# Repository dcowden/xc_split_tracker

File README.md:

# XC Tracker files

**xc_direct_esp32_receiver** uses an esp for compute, and an nrf52840 that reads the radio packets and sends them via uart
**xc_direct_radio_test_rx**  is the receiver 
**xc_direct_radio_test_tx** is  the transmitter
**xc_patriot_logger_nrf52840** is a try using ONLY the nrf52840, but i realized you cant use the radio and BLE, and since it also has no wifi its not a way forward
**xc_wifi_tracker_board_tests** Tests usingthe wifi tracker board-- really just getting the gps module working and printong on the screen

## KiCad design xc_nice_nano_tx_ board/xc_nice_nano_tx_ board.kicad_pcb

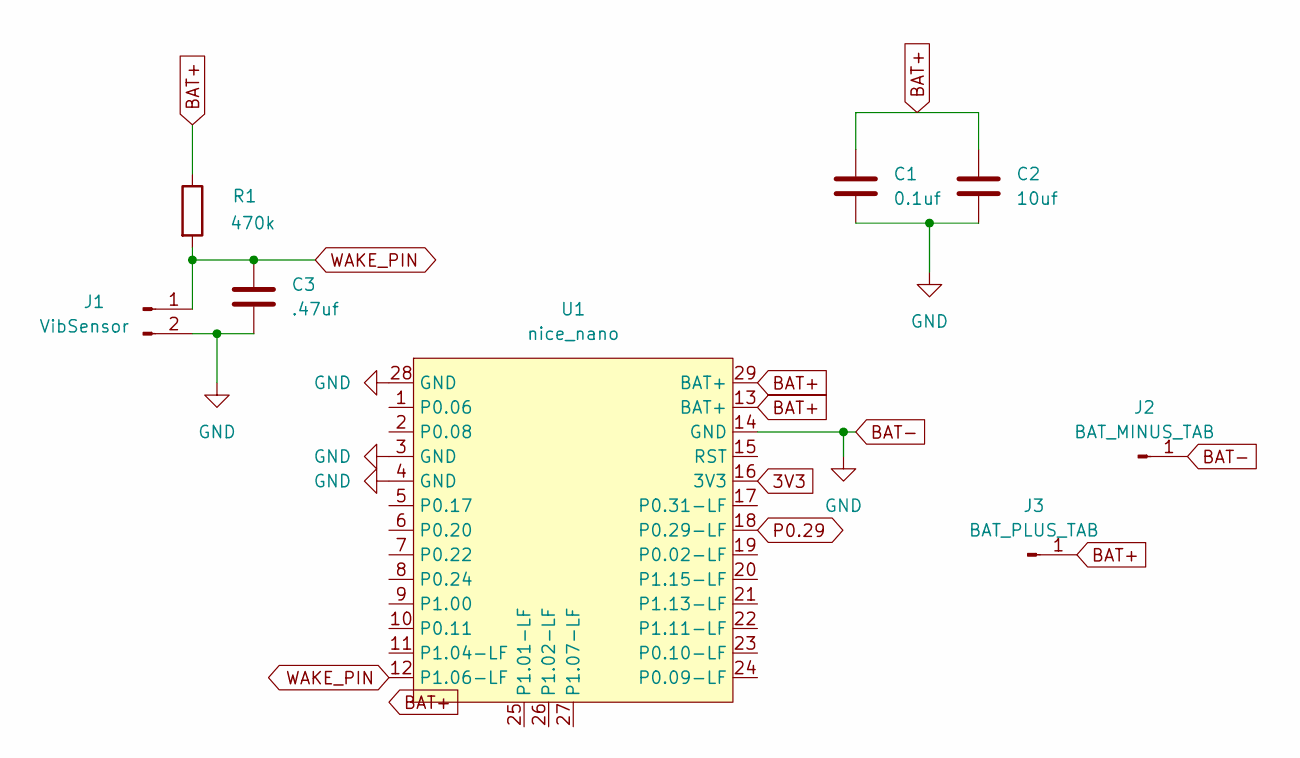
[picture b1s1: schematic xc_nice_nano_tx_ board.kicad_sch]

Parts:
C1: 0.1uf; C_0603_1608Metric
C2: 10uf; C_0603_1608Metric
C3: .47uf; C_0603_1608Metric
J1: VibSensor; CP_Radial_D5.0mm_P2.50mm
J2: BAT_MINUS_TAB; PinSocket_1x01_P2.54mm_Vertical
J3: BAT_PLUS_TAB; PinSocket_1x01_P2.54mm_Vertical
R1: 470k; R_0603_1608Metric
U1: nice_nano; nice_nano_AH_USBup

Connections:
3V3: U1.16 (3V3)
BAT+: C1.1, C2.1, J3.1, R1.1, U1.13 (BAT+), U1.29 (BAT+)
BAT-: C1.2, C2.2, C3.2, J1.2, J2.1, U1.3 (GND), U1.4 (GND), U1.14 (GND), U1.28 (GND)
P0.29: U1.18 (P0.29-LF)
WAKE_PIN: C3.1, J1.1, R1.2, U1.12 (P1.06-LF)

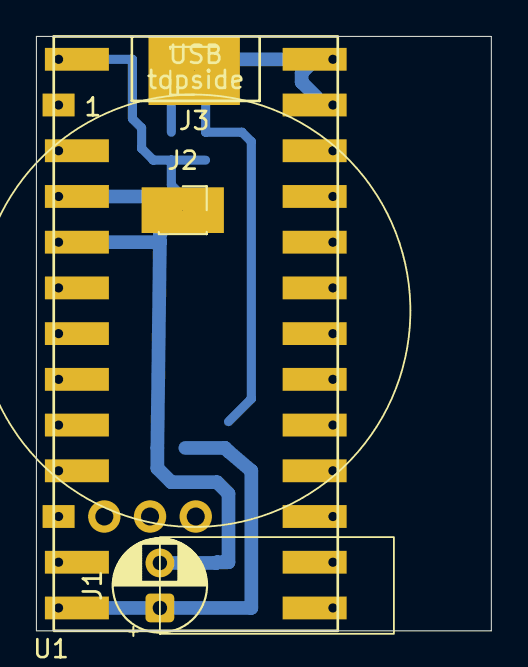
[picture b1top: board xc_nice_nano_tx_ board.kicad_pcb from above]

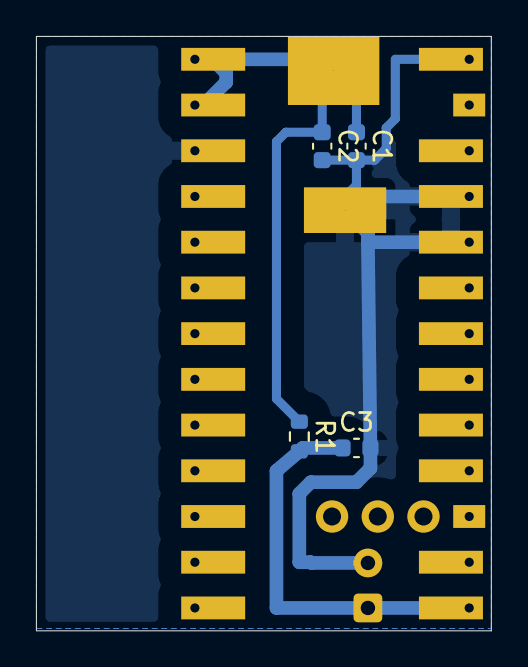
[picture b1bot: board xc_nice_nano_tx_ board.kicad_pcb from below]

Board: 2 copper layers, 25.3 x 33.0 mm, 8 parts (4 on the bottom side), 3 nets.

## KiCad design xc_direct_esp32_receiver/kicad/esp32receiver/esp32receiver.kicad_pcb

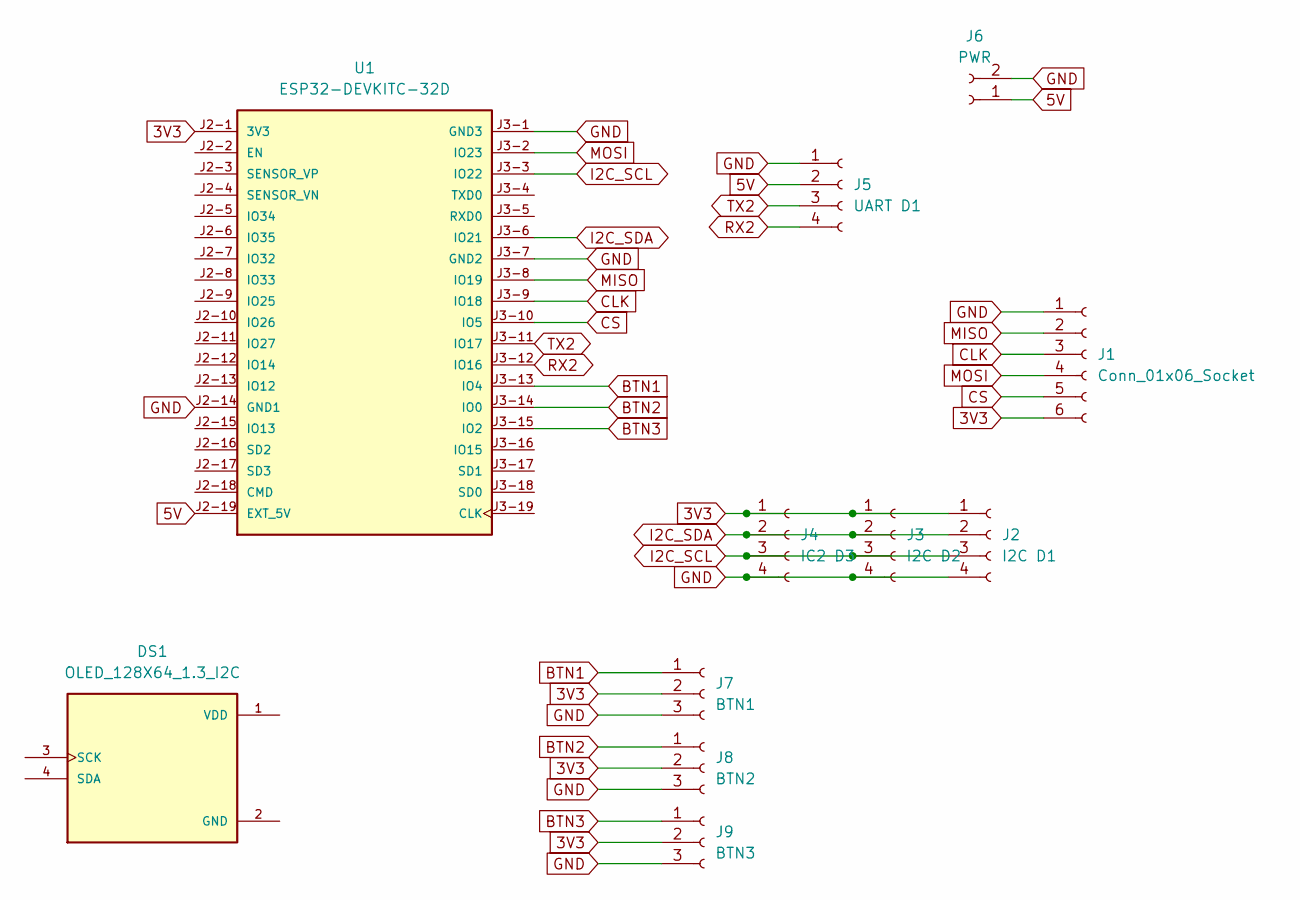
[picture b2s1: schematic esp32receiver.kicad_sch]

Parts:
DS1: OLED_128X64_1.3_I2C; LCD_OLED_128X64_1.3_I2C; PARTREV NA
J1: Conn_01x06_Socket; JST_EH_B6B-EH-A_1x06_P2.50mm_Vertical
J2: I2C D1; PinHeader_1x04_P2.00mm_Vertical_SMD_Pin1Left
J3: I2C D2; PinHeader_1x04_P2.00mm_Vertical_SMD_Pin1Left
J4: IC2 D3; PinHeader_1x04_P2.00mm_Vertical_SMD_Pin1Left
J5: UART D1; PinHeader_1x04_P2.00mm_Vertical_SMD_Pin1Left
J6: PWR; JST_EH_B2B-EH-A_1x02_P2.50mm_Vertical
J7: BTN1; PinHeader_1x03_P2.00mm_Vertical_SMD_Pin1Left
J8: BTN2; PinHeader_1x03_P2.00mm_Vertical_SMD_Pin1Left
J9: BTN3; PinHeader_1x03_P2.00mm_Vertical_SMD_Pin1Left
U1: ESP32-DEVKITC-32D; MODULE_ESP32-DEVKITC-32D; PARTREV V4

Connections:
3V3: J1.6, J2.1, J3.1, J4.1, J7.2, J8.2, J9.2, U1.J2-1 (3V3)
5V: J5.2, J6.1, U1.J2-19 (EXT_5V)
BTN1: J7.1, U1.J3-13 (IO4)
BTN2: J8.1, U1.J3-14 (IO0)
BTN3: J9.1, U1.J3-15 (IO2)
CLK: J1.3, U1.J3-9 (IO18)
CS: J1.5, U1.J3-10 (IO5)
GND: J1.1, J2.4, J3.4, J4.4, J5.1, J6.2, J7.3, J8.3, J9.3, U1.J2-14 (GND1), U1.J3-1 (GND3), U1.J3-7 (GND2)
I2C_SCL: J2.3, J3.3, J4.3, U1.J3-3 (IO22)
I2C_SDA: J2.2, J3.2, J4.2, U1.J3-6 (IO21)
MISO: J1.2, U1.J3-8 (IO19)
MOSI: J1.4, U1.J3-2 (IO23)
RX2: J5.4, U1.J3-12 (IO16)
TX2: J5.3, U1.J3-11 (IO17)

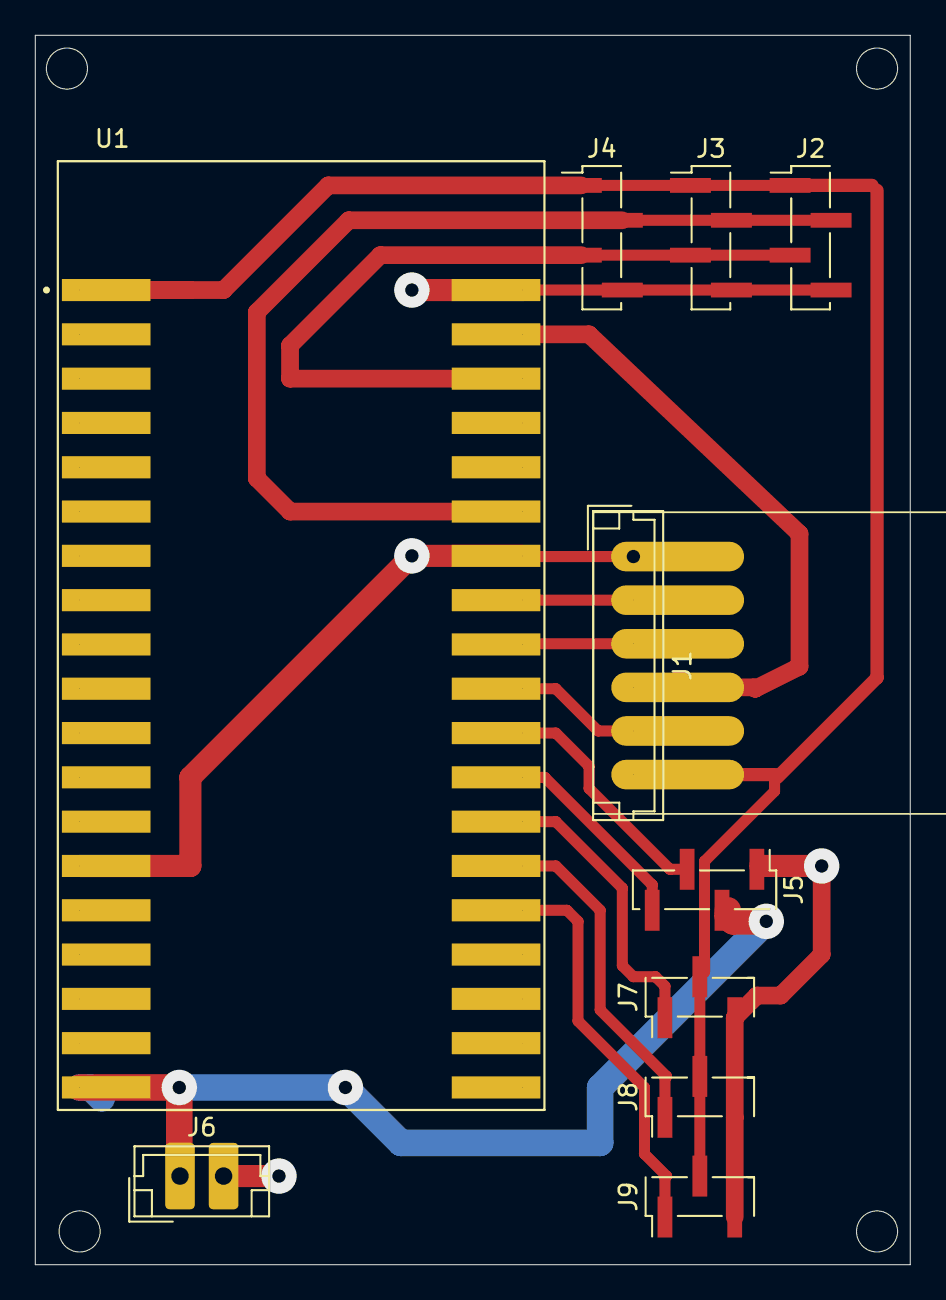
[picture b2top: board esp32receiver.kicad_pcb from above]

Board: 2 copper layers, 50.2 x 70.5 mm, 10 parts (0 on the bottom side), 14 nets.

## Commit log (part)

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2025-12-13 inital version
2025-12-21 starting point for fancy checker splash
2025-12-21 starting point for splash
2025-12-27 added battery monitoring
2025-12-27 time-based sd card files. ready for motion trigger on tx
2025-12-29 added motion battery wakeup on tag
2025-12-30 mostly there. still need to prove out wakeup on nicenano
2025-12-31 add battery flash indicator
2025-12-31 tweaked board. i think we're ready
2026-01-04 i built this version
2026-01-04 ready for first ben test!
